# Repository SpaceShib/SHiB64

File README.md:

# SHiB64
A simple 8-Bit computer for education and hobbyists

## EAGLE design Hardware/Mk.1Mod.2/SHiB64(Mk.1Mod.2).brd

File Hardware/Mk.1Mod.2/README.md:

# SHiB64 Mk.1 Mod.2

The first completed SHiB64 with surface mount ICs

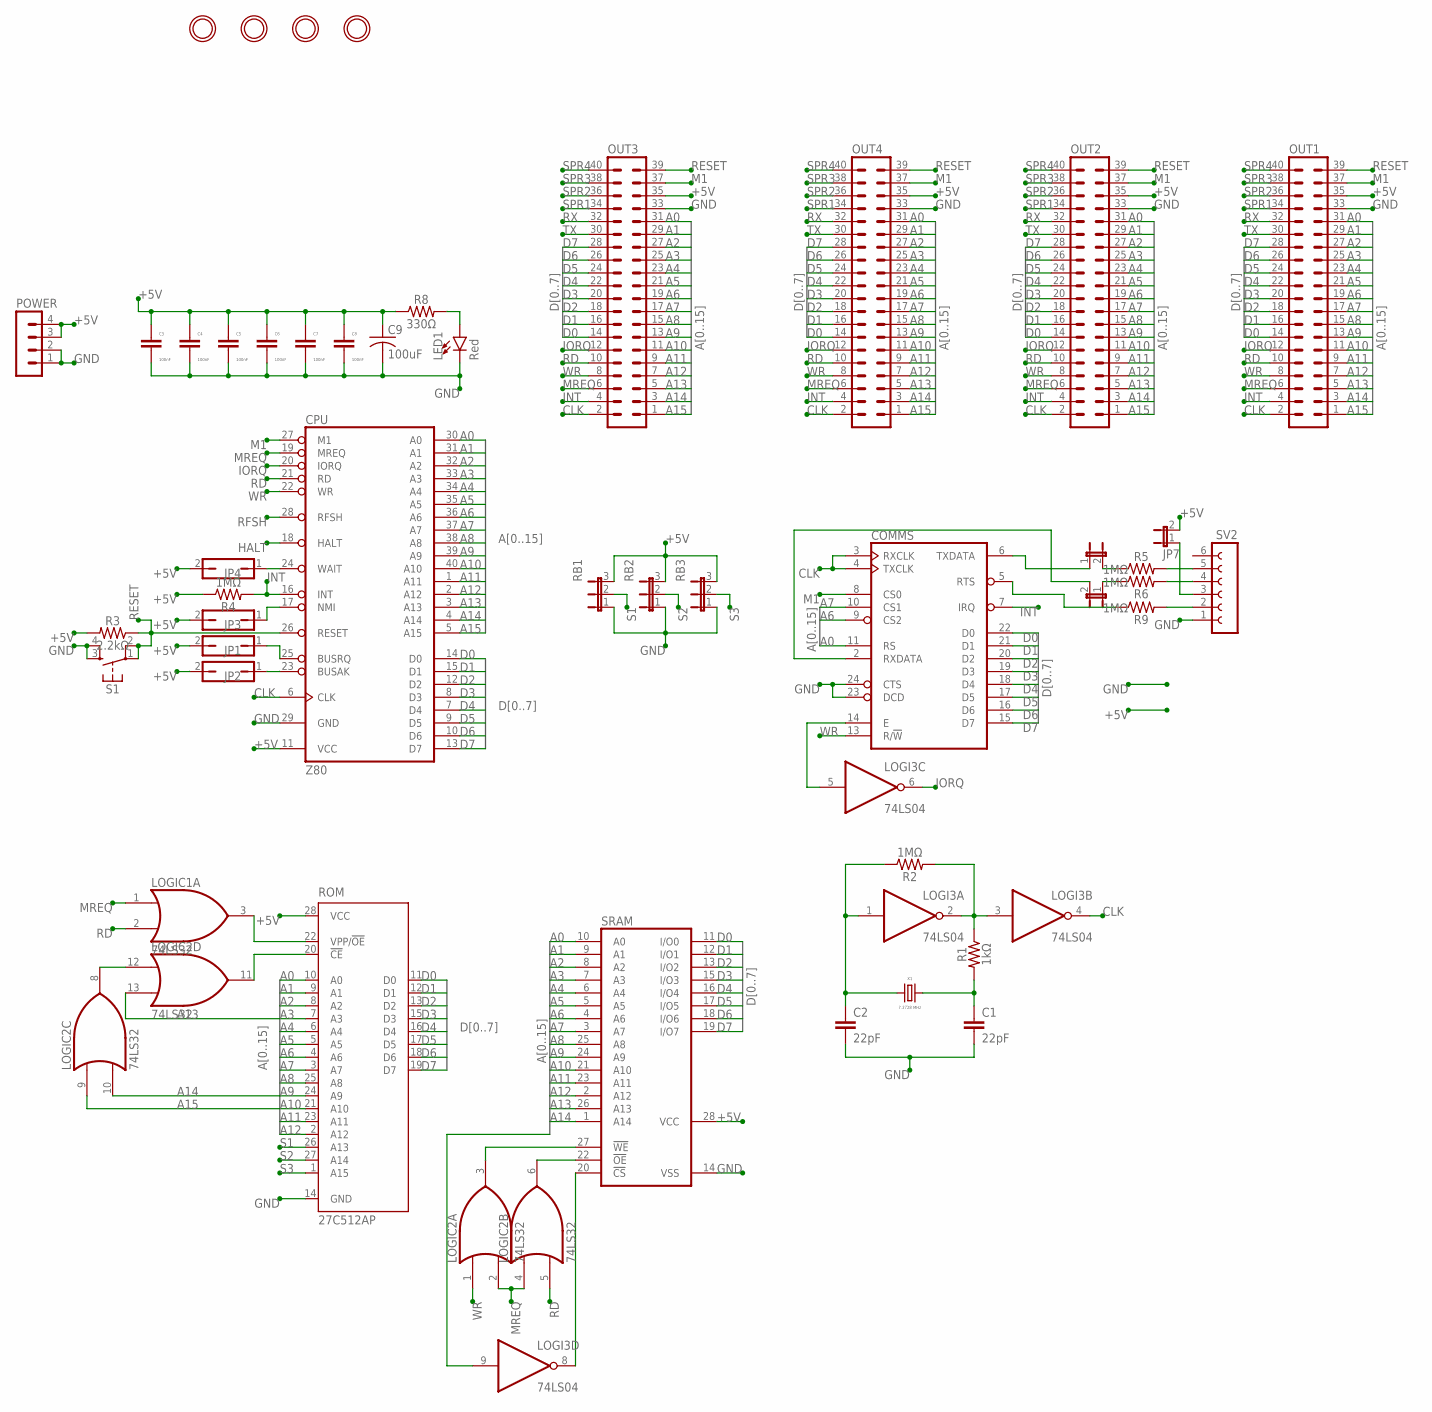
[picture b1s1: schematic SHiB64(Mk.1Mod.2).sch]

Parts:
C1, C2: 22pF; CAP-PTH-2.54
C3, C4, C5, C6, C7, C8: 100nF; C1206
C9: 100uF; C1206
COMMS: 6850; DIL24
CPU: Z80; DIL40
JP1, JP2, JP3, JP4: JP1Q; JP1
JP5, JP6, JP7: JP1E; JP1
LED1: Red; LED_1206
LOGI3: 74LS04; SO14
LOGIC1, LOGIC2: 74LS32; SO14
OUT1, OUT2, OUT3, OUT4: MA20-2
POWER: MA04-1
R1: 1kΩ; R1206
R2, R4, R5, R6, R9: 1MΩ; R1206
R3: 2.2kΩ; R1206
R8: 330Ω; R1206
RB1, RB2, RB3: JP2E; JP2
ROM: 27C512AP; DIL28-6
S1: MOMENTARY_BUTTONS6MMSMALL; TACTILE_SWITCH_PTH_6.0MM
SRAM: 62256P; DIL28-6
SV2: FE06-1; FE06
U$1, U$2, U$3, U$4: MOUNTING_HOLE; MOUNTINGHOLE_3.2MM_PLATEDTHIN
X1: 7.3728 MHz; HC49US

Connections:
+5V: C3.1, C4.1, C5.1, C6.1, C7.1, C8.1, C9.1, COMMS.12 (VCC), CPU.11 (VCC), JP1.2, JP2.2, JP3.2, JP4.2, JP7.2, LOGI3.14 (VCC), LOGIC1.14 (VCC), LOGIC2.14 (VCC), OUT1.35, OUT2.35, OUT3.35, OUT4.35, POWER.3, POWER.4, R3.2, R4.1, R8.1, RB1.3, RB2.3, RB3.3, ROM.28 (VCC), SRAM.28 (VCC)
A0: COMMS.11 (RS), CPU.30 (A0), OUT1.31, OUT2.31, OUT3.31, OUT4.31, ROM.10 (A0), SRAM.10 (A0)
A1: CPU.31 (A1), OUT1.29, OUT2.29, OUT3.29, OUT4.29, ROM.9 (A1), SRAM.9 (A1)
A2: CPU.32 (A2), OUT1.27, OUT2.27, OUT3.27, OUT4.27, ROM.8 (A2), SRAM.8 (A2)
A3: CPU.33 (A3), OUT1.25, OUT2.25, OUT3.25, OUT4.25, ROM.7 (A3), SRAM.7 (A3)
A4: CPU.34 (A4), OUT1.23, OUT2.23, OUT3.23, OUT4.23, ROM.6 (A4), SRAM.6 (A4)
A5: CPU.35 (A5), OUT1.21, OUT2.21, OUT3.21, OUT4.21, ROM.5 (A5), SRAM.5 (A5)
A6: COMMS.9 (CS2), CPU.36 (A6), OUT1.19, OUT2.19, OUT3.19, OUT4.19, ROM.4 (A6), SRAM.4 (A6)
A7: COMMS.10 (CS1), CPU.37 (A7), OUT1.17, OUT2.17, OUT3.17, OUT4.17, ROM.3 (A7), SRAM.3 (A7)
A8: CPU.38 (A8), OUT1.15, OUT2.15, OUT3.15, OUT4.15, ROM.25 (A8), SRAM.25 (A8)
A9: CPU.39 (A9), OUT1.13, OUT2.13, OUT3.13, OUT4.13, ROM.24 (A9), SRAM.24 (A9)
A10: CPU.40 (A10), OUT1.11, OUT2.11, OUT3.11, OUT4.11, ROM.21 (A10), SRAM.21 (A10)
A11: CPU.1 (A11), OUT1.9, OUT2.9, OUT3.9, OUT4.9, ROM.23 (A11), SRAM.23 (A11)
A12: CPU.2 (A12), OUT1.7, OUT2.7, OUT3.7, OUT4.7, ROM.2 (A12), SRAM.2 (A12)
A13: CPU.3 (A13), LOGIC2.13 (I1), OUT1.5, OUT2.5, OUT3.5, OUT4.5, SRAM.26 (A13)
A14: CPU.4 (A14), LOGIC2.10 (I1), OUT1.3, OUT2.3, OUT3.3, OUT4.3, SRAM.1 (A14)
A15: CPU.5 (A15), LOGI3.9 (I), LOGIC2.9 (I0), OUT1.1, OUT2.1, OUT3.1, OUT4.1
CLK: COMMS.3 (RXCLK), COMMS.4 (TXCLK), CPU.6 (CLK), LOGI3.4 (O), OUT1.2, OUT2.2, OUT3.2, OUT4.2
D0: COMMS.22 (D0), CPU.14 (D0), OUT1.14, OUT2.14, OUT3.14, OUT4.14, ROM.11 (D0), SRAM.11 (I/O0)
D1: COMMS.21 (D1), CPU.15 (D1), OUT1.16, OUT2.16, OUT3.16, OUT4.16, ROM.12 (D1), SRAM.12 (I/O1)
D2: COMMS.20 (D2), CPU.12 (D2), OUT1.18, OUT2.18, OUT3.18, OUT4.18, ROM.13 (D2), SRAM.13 (I/O2)
D3: COMMS.19 (D3), CPU.8 (D3), OUT1.20, OUT2.20, OUT3.20, OUT4.20, ROM.15 (D3), SRAM.15 (I/O3)
D4: COMMS.18 (D4), CPU.7 (D4), OUT1.22, OUT2.22, OUT3.22, OUT4.22, ROM.16 (D4), SRAM.16 (I/O4)
D5: COMMS.17 (D5), CPU.9 (D5), OUT1.24, OUT2.24, OUT3.24, OUT4.24, ROM.17 (D5), SRAM.17 (I/O5)
D6: COMMS.16 (D6), CPU.10 (D6), OUT1.26, OUT2.26, OUT3.26, OUT4.26, ROM.18 (D6), SRAM.18 (I/O6)
D7: COMMS.15 (D7), CPU.13 (D7), OUT1.28, OUT2.28, OUT3.28, OUT4.28, ROM.19 (D7), SRAM.19 (I/O7)
GND: C1.2, C2.2, C3.2, C4.2, C5.2, C6.2, C7.2, C8.2, C9.2, COMMS.1 (VSS), COMMS.23 (DCD), COMMS.24 (CTS), CPU.29 (GND), LED1.- (C), LOGI3.7 (GND), LOGIC1.7 (GND), LOGIC2.7 (GND), OUT1.33, OUT2.33, OUT3.33, OUT4.33, POWER.1, POWER.2, RB1.1, RB2.1, RB3.1, ROM.14 (GND), S1.3 (S), S1.4 (S1), SRAM.14 (VSS), SV2.1
HALT: CPU.18 (HALT)
INT: COMMS.7 (IRQ), CPU.16 (INT), OUT1.4, OUT2.4, OUT3.4, OUT4.4, R4.2
IORQ: CPU.20 (IORQ), LOGI3.6 (O), OUT1.12, OUT2.12, OUT3.12, OUT4.12
M1: COMMS.8 (CS0), CPU.27 (M1), OUT1.37, OUT2.37, OUT3.37, OUT4.37
MREQ: CPU.19 (MREQ), LOGIC1.1 (I0), LOGIC2.2 (I1), LOGIC2.4 (I0), OUT1.6, OUT2.6, OUT3.6, OUT4.6
unnamed: C1.1, R1.2, X1.2
unnamed: C2.1, LOGI3.1 (I), R2.1, X1.1
unnamed: LOGI3.2 (O), LOGI3.3 (I), R1.1, R2.2
unnamed: CPU.25 (BUSRQ), JP1.1
unnamed: CPU.23 (BUSAK), JP2.1
unnamed: CPU.17 (NMI), JP3.1
unnamed: CPU.24 (WAIT), JP4.1
unnamed: LOGIC1.3 (O), ROM.22 (VPP/!OE)
unnamed: LOGIC2.11 (O), ROM.20 (!CE)
unnamed: LOGIC2.8 (O), LOGIC2.12 (I0)
unnamed: JP5.2, R5.1
unnamed: COMMS.14 (E), LOGI3.5 (I)
unnamed: JP6.1, R6.1
unnamed: COMMS.6 (TXDATA), JP5.1
unnamed: R6.2, SV2.4
unnamed: R5.2, SV2.5
unnamed: COMMS.2 (RXDATA), JP6.2
unnamed: COMMS.5 (RTS), R9.1
unnamed: JP7.1, SV2.3
unnamed: R9.2, SV2.2
unnamed: LOGI3.8 (O), SRAM.20 (!CS)
unnamed: LOGIC2.6 (O), SRAM.22 (!OE)
unnamed: LOGIC2.3 (O), SRAM.27 (!WE)
unnamed: LED1.+ (A), R8.2
RD: CPU.21 (RD), LOGIC1.2 (I1), LOGIC2.5 (I1), OUT1.10, OUT2.10, OUT3.10, OUT4.10
RESET: CPU.26 (RESET), OUT1.39, OUT2.39, OUT3.39, OUT4.39, R3.1, S1.1, S1.2 (P1)
RFSH: CPU.28 (RFSH)
RX: OUT1.32, OUT2.32, OUT3.32, OUT4.32
S1: RB1.2, ROM.26 (A13)
S2: RB2.2, ROM.27 (A14)
S3: RB3.2, ROM.1 (A15)
SPR1: OUT1.34, OUT2.34, OUT3.34, OUT4.34
SPR2: OUT1.36, OUT2.36, OUT3.36, OUT4.36
SPR3: OUT1.38, OUT2.38, OUT3.38, OUT4.38
SPR4: OUT1.40, OUT2.40, OUT3.40, OUT4.40
TX: OUT1.30, OUT2.30, OUT3.30, OUT4.30
WR: COMMS.13 (R/!W), CPU.22 (WR), LOGIC2.1 (I0), OUT1.8, OUT2.8, OUT3.8, OUT4.8

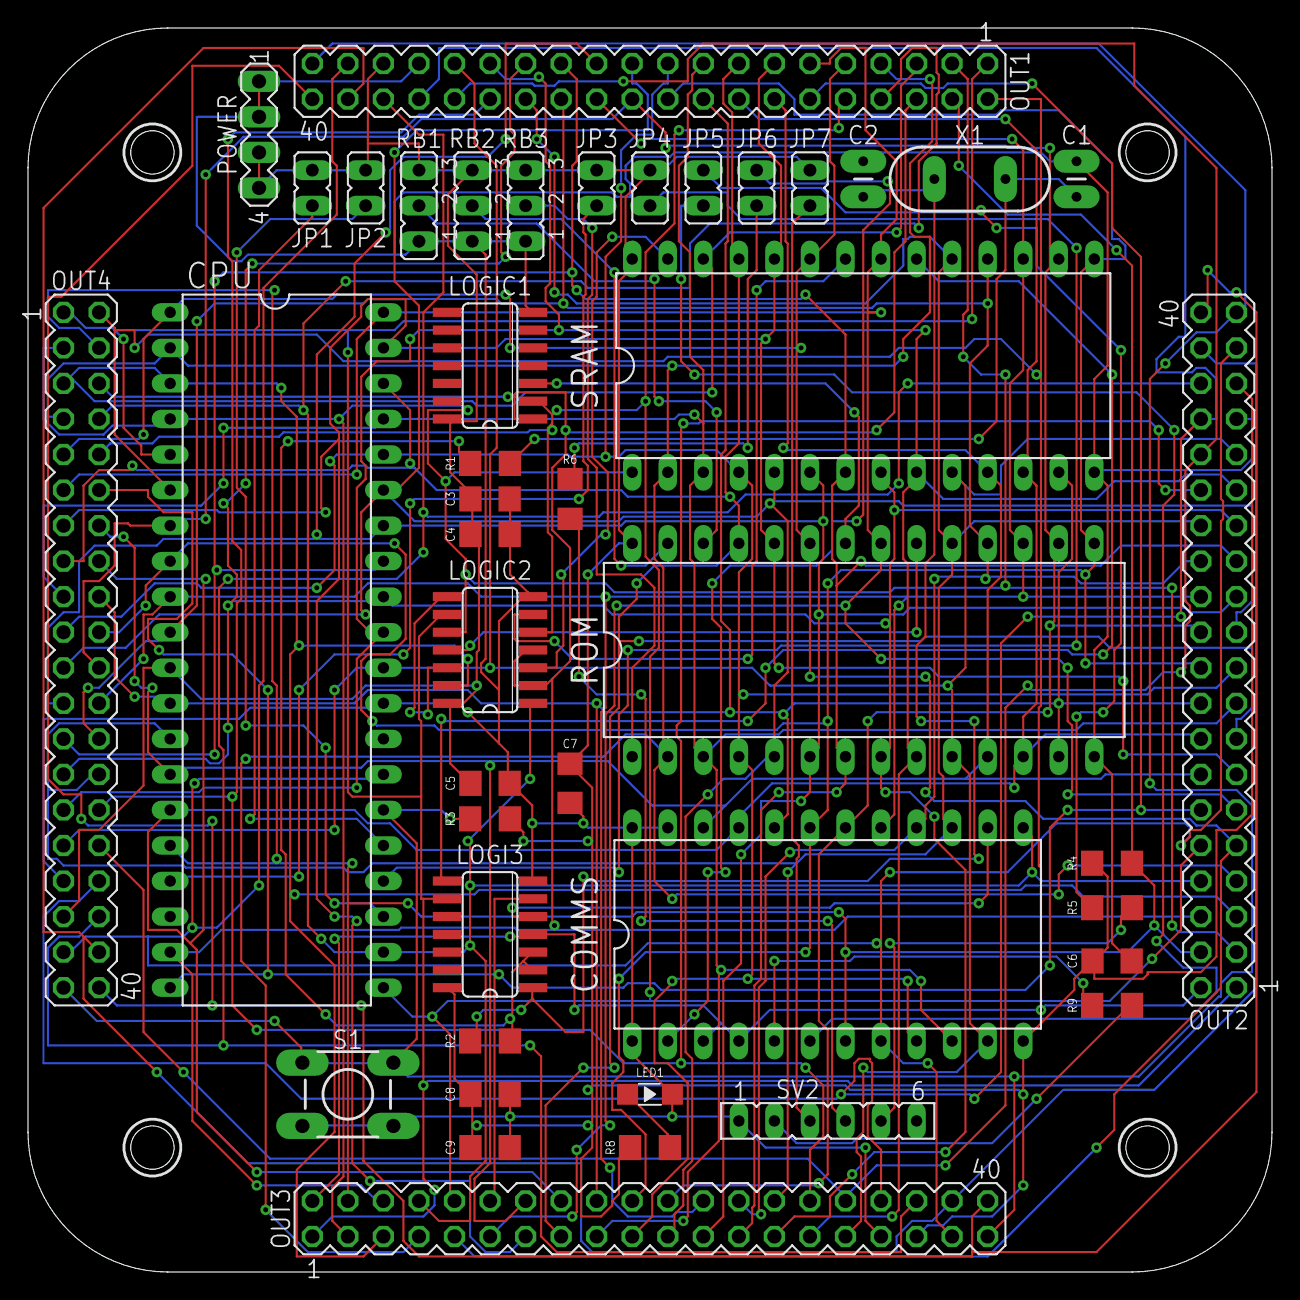
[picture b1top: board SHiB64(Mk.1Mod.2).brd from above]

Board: 2 copper layers, 88.9 x 88.9 mm, 47 parts (0 on the bottom side), 67 nets.
